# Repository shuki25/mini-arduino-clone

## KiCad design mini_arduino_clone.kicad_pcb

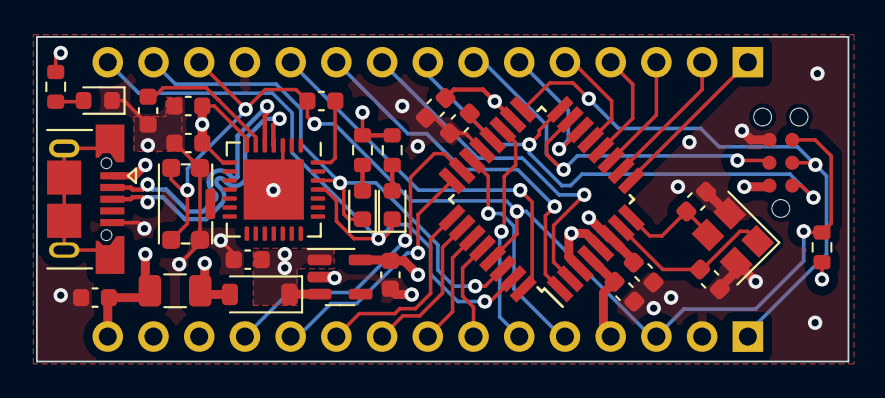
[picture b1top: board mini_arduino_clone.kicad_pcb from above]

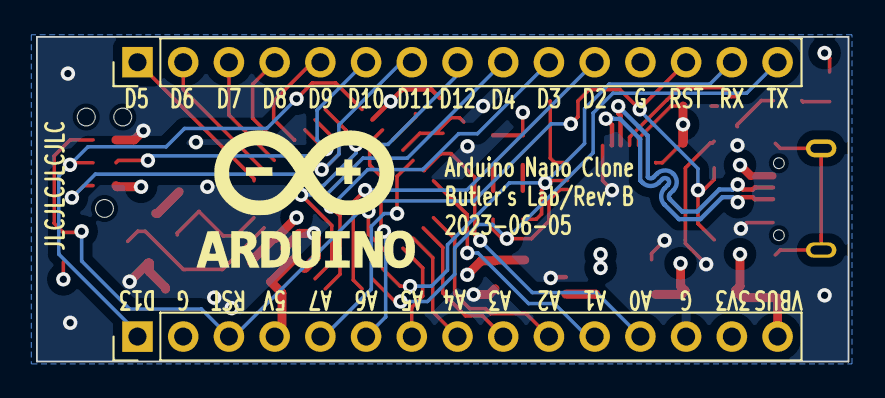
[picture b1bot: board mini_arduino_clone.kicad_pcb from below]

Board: 4 copper layers, 45.1 x 18.0 mm, 31 parts (2 on the bottom side), 38 nets.

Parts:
C101, C103, C104, C106, C108, C302, C303: 100nF; C_0603_1608Metric
C102, C301: 1uF; C_0603_1608Metric
C105, C107: 12pF; C_0603_1608Metric
C201: 22uF; C_0603_1608Metric
C202: 4.7uF; C_0603_1608Metric
D1: B5819W; D_SOD-123
D101: Green; LED_0603_1608Metric
D102: Blue; LED_0603_1608Metric
D103: Red; LED_0603_1608Metric
F101: Polyfuse_Small; Fuse_1206_3216Metric
J101: USB_B_Micro; USB_Micro-B_XKB_U254-051T-4BH83-F1S
J102: Conn_02x03_Odd_Even; TC2030-IDC-NL
J103, J104: Conn_01x13; PinHeader_1x15_P2.54mm_Vertical
R103: 10K; R_0603_1608Metric
R104, R105, R106: 2K2; R_0603_1608Metric
SW101: SW_Push; SW_SPST_KMR221GLFS
U101: ATmega328P-AU; TQFP-32_7x7mm_P0.8mm
U201: XC6220B331MR-G; SOT-23-5
U301: CP2102-GMR; QFN-28-1EP_5x5mm_P0.5mm_EP3.35x3.35mm
Y101: 16MHz; Crystal_SMD_3225-4Pin_3.2x2.5mm

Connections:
+3V3: C202.1, J104.14, U201.5 (VOUT)
+5V: C103.1, C104.1, C106.1, C201.2, D1.1 (K), J102.2 (VCC), J104.4, R103.1, R104.1, R105.1, R106.1, U101.4 (VCC), U101.6 (VCC), U101.18 (AVCC), U201.1 (VIN), U201.3 (CE)
/A0: J104.12, U101.23 (PC0)
/A1: J104.11, U101.24 (PC1)
/A2: J104.10, U101.25 (PC2)
/A3: J104.9, U101.26 (PC3)
/A4/~SDA: J104.8, U101.27 (PC4)
/A5/SCL: J104.7, U101.28 (PC5)
/A6: J104.6, U101.19 (ADC6)
/A7: J104.5, U101.22 (ADC7)
/AREF: C101.1, U101.20 (AREF)
/D0/RX: D101.1 (K), J103.14, U101.30 (PD0), U301.26 (TXD)
/D1/TX: D102.1 (K), J103.15, U101.31 (PD1), U301.25 (RXD)
/D2: J103.11, U101.32 (PD2)
/D3: J103.10, U101.1 (PD3)
/D4: J103.9, U101.2 (PD4)
/D5: J103.1, U101.9 (PD5)
/D6: J103.2, U101.10 (PD6)
/D7: J103.3, U101.11 (PD7)
/D8: J103.4, U101.12 (PB0)
/D9: J103.5, U101.13 (PB1)
/D10: J103.6, U101.14 (PB2)
/D11/MOSI: J102.4 (MOSI), J103.7, U101.15 (PB3)
/D12/MISO: J102.1 (MISO), J103.8, U101.16 (PB4)
/D13/SCK: J102.3 (SCK), J104.1, U101.17 (PB5)
/DTR: C108.2, U301.28 (~DTR)
/D_N: J101.2 (D-), U301.5 (D-)
/D_P: J101.3 (D+), U301.4 (D+)
/USB_UART/VBUS: C301.1, C302.1, D1.2 (A), F101.2, U301.7 (VREGIN), U301.8 (VBUS)
/XTAL1: C105.1, U101.7 (XTAL1/PB6), Y101.1
/XTAL2: C107.1, U101.8 (XTAL2/PB7), Y101.3
/~RESET: C108.1, J102.5 (~RST), J103.13, J104.3, R103.2, SW101.2, U101.29 (~RESET/PC6)
GND: C101.2, C102.2, C103.2, C104.2, C105.2, C106.2, C107.2, C201.1, C202.2, C301.2, C302.2, C303.2, D103.1 (K), J101.5 (GND), J102.6 (GND), J103.12, J104.2, J104.13, SW101.1, U101.3 (GND), U101.5 (GND), U101.21 (GND), U201.2 (GND), U301.3 (GND), U301.29 (GND), Y101.2, Y101.4
unnamed: D101.2 (A), R104.2
unnamed: D102.2 (A), R105.2
unnamed: D103.2 (A), R106.2
unnamed: C303.1, U301.6 (VDD)
VBUS: C102.1, F101.1, J101.1 (VBUS), J104.15

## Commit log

2023-03-17 update pcb layout
2023-03-18 update layout and schematics
2023-03-18 add production files
2023-03-26 update bom/exclude settings
2023-03-26 update production files
2023-03-26 remove old production folder/files
2023-03-26 add 3d models and dimensions
2023-05-16 update parts
2023-06-02 fix pin assignments on crystal
2023-06-05 update settings
